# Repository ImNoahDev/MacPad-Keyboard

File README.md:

# The MacPad

The MacPad is a full sized keyboard designed for use with a Mac. The keyboard has 2 rotary encoders and a single fader for custom controls. The keyboard is designed to be used with QMK,

It can use any Alps or Cherry MX switches with optional through hole LEDs for backlighting.

## Assembly

The Plate must first be soldered underneath the switches (see plate.ai)

The PCB screws into the base with M3 screws and the top of the case screws ontop.

QMK firmware + configuration must be flashed using the macpad.hex file. The reset button can be pressed on the keyboard to put it into flashing mode and to flash the firmware. the F18 button can then be used as a reset button after the initial flash.

## BOM

| Item name         | Item price | Item use                                               | URL                                                                    |
| ----------------- | ---------- | ------------------------------------------------------ | ---------------------------------------------------------------------- |
| PCB               | $34        | PCB manufacture                                        | pcbway.com                                                             |
| PCB components    | $13        | Assemble controller on keyboard + rotary encoder/fader | pcbway.com                                                             |
| PCB Assembly      | $30        | Assemble PCB                                           | pcbway.com                                                             |
| Keyboard switches | $30        | Make the keyboard keyboard                             | [Keyswitches](https://www.keychron.uk/products/keychron-super-switch)  |
| Black fillament   | $24        | Print the case                                         | https://uk.store.bambulab.com/products/petg-hf?id=42010450329660       |
| Battery           | $10.78     | Battery power                                          | https://www.amazon.co.uk/EEMB-Battery-rechargeable-Connector-Certified |
| Total:            | $142.71    |                                                        |                                                                        |

## PCB component breakdown

| Designator                                                                                           | Quantity | Value                       | Footprint                               | Package | MPN                | DNP | Mount_Type | Description                                                                            | Price   | Total   | URL                                                                       |
| ---------------------------------------------------------------------------------------------------- | -------- | --------------------------- | --------------------------------------- | ------- | ------------------ | --- | ---------- | -------------------------------------------------------------------------------------- | ------- | ------- | ------------------------------------------------------------------------- |
| C1, C2                                                                                               | 2        | 22pF                        | C_0805_2012Metric                       |         |                    |     | smt        |                                                                                        | $0.0011 | $0.0022 | https://jlcpcb.com/partdetail/1907-0402CG220J500NT/C1555                  |
| C3                                                                                                   | 1        | 1uF                         | C_0805_2012Metric                       |         |                    |     | smt        |                                                                                        | $0.0032 | $0.0064 | https://jlcpcb.com/partdetail/1944-CL10A105KO8NNNC/C1592                  |
| C4, C5, C6                                                                                           | 3        | 0.1uF                       | C_0805_2012Metric                       |         |                    |     | smt        |                                                                                        | $0.0011 | $0.0033 | https://jlcpcb.com/partdetail/1877-CL05B104KO5NNNC/C1525                  |
| C7                                                                                                   | 1        | 10uF                        | C_0805_2012Metric                       |         |                    |     | smt        |                                                                                        | $0.0028 | $0.0028 | https://jlcpcb.com/partdetail/2043-CL10A106MQ8NNNC/C1691                  |
| D_0, D_1, D_10, D_100, D_101, D_102, D_103, D_104, D_105, D_106, D_107, D_108, D_11, D_12, D_13, D_14, D_15, D_16, D_17, D_18, D_19, D_2, D_20, D_21, D_22, D_23, D_24, D_25, D_26, D_27, D_28, D_29, D_3, D_30, D_31, D_32, D_33, D_34, D_35, D_36, D_37, D_38, D_39, D_4, D_40, D_41, D_42, D_43, D_44, D_45, D_46, D_47, D_48, D_49, D_5, D_50, D_51, D_52, D_53, D_54, D_55, D_56, D_57, D_58, D_59, D_6, D_60, D_61, D_62, D_63, D_64, D_65, D_66, D_67, D_68, D_69, D_7, D_70, D_71, D_72, D_73, D_74, D_75, D_76, D_77, D_78, D_79, D_8, D_80, D_81, D_82, D_83, D_84, D_85, D_86, D_87, D_88, D_89, D_9, D_90, D_91, D_92, D_93, D_94, D_95, D_96, D_97, D_98, D_99 | 109      | D                           | D_SOD-123                               |         |                    |     | smt        |                                                                                        | $0.0052 | $0.57   | https://jlcpcb.com/partdetail/Shunye-ES1D_SOD_123FL/C7370889              |
| F1                                                                                                   | 1        | 500mA                       | Fuse_1206_3216Metric                    |         |                    |     | smt        |                                                                                        | $0.0365 | $0.0365 | https://jlcpcb.com/partdetail/JlcpcbAssembly-FUSE/C9900021114             |
| J1                                                                                                   | 1        | USB_C_Receptacle_USB2.0_14P | USB_C_Receptacle_HCTL_HC-TYPE-C-16P-01A |         |                    |     | smt        | USB 2.0-only 14P Type-C Receptacle connector                                           | $0.0365 | $0.0365 | https://jlcpcb.com/partdetail/JlcpcbAssembly-14P/C9900117666              |
| Q1                                                                                                   | 1        | AO3400A                     | SOT-23                                  |         |                    |     | smt        | 30V Vds, 5.7A Id, N-Channel MOSFET, SOT-23                                             | $0.0428 | $0.0428 | https://jlcpcb.com/partdetail/Alpha_OmegaSemicon-AO3400A/C20917           |
| R1, R6, R7                                                                                           | 3        | 10k                         | R_0805_2012Metric                       |         |                    |     | smt        | Resistor                                                                               | $0.0013 | $0.0039 | https://jlcpcb.com/partdetail/1841-1206W4J0103T5E/C1489                   |
| R10, R100, R101, R102, R103, R104, R105, R106, R107, R108, R109, R11, R110, R111, R112, R113, R114, R115, R116, R117, R118, R12, R13, R14, R15, R16, R17, R18, R19, R20, R21, R22, R23, R24, R25, R26, R27, R28, R29, R30, R31, R32, R33, R34, R35, R36, R37, R38, R39, R40, R41, R42, R43, R44, R45, R46, R47, R48, R49, R50, R51, R52, R53, R54, R55, R56, R57, R58, R59, R60, R61, R62, R63, R64, R65, R66, R67, R68, R69, R70, R71, R72, R73, R74, R75, R76, R77, R78, R79, R80, R81, R82, R83, R84, R85, R86, R87, R88, R89, R90, R91, R92, R93, R94, R95, R96, R97, R98, R99 | 109      | 120                         | R_0805_2012Metric                       |         |                    |     | smt        | Resistor                                                                               | $0.0008 | $0.0872 | https://jlcpcb.com/partdetail/23514-0603WAF1200T5E/C22787                 |
| R2, R3                                                                                               | 2        | 5.1k                        | R_0805_2012Metric                       |         |                    |     | smt        |                                                                                        | $0.0007 | $0.0014 | https://jlcpcb.com/partdetail/Yageo-RC0603JR075K1L/C14677                 |
| R4, R5                                                                                               | 2        | 22                          | R_0805_2012Metric                       |         |                    |     | smt        |                                                                                        | $0.0005 | $0.001  | https://jlcpcb.com/partdetail/1555-0603WAJ0220T5E/C1203                   |
| R8                                                                                                   | 1        | 220                         | R_0805_2012Metric                       |         |                    |     | smt        | Resistor                                                                               | $0.0004 | $0.0004 | https://jlcpcb.com/partdetail/1463-RC02W221JT/C1111                       |
| SW1                                                                                                  | 1        | SW_Push                     | SKQG-1155865                            |         |                    |     | smt        |                                                                                        | $0.2385 | $0.2385 | https://jlcpcb.com/partdetail/Panasonic-EVQQ2B03W/C79178                  |
| U1                                                                                                   | 1        | RF-BM-ND06                  |                                         |         |                    |     | smt        |                                                                                        | $5      | $5      | https://jlcpcb.com/partdetail/rfstar-RF_BMND06/C5125838                   |
| U2, U3                                                                                               | 2        | EC11E18244A5                | EC11E18244A5_ALPS                       |         |                    |     | tht        |                                                                                        | $1.9785 | $3.96   | https://jlcpcb.com/partdetail/Alpsalpine-EC11E18244A5/C255515             |
| VR1                                                                                                  | 1        | PTB0143-2010BPB103          | PTB01432010BPB103                       |         | PTB0143-2010BPB103 |     | tht        | Bourns PTB0143-2010BPB103 1 Gang Slide Carbon Potentiometer, 10k, +/-20%, 0.5W, Linear | $5.5140 | $5.5140 | https://jlcpcb.com/partdetail/Bourns-PTB01432010BPB103/C17183742          |
| Y1                                                                                                   | 1        | 16MHz                       | Crystal_SMD_3225-4Pin_3.2x2.5mm         |         |                    |     | smt        |                                                                                        | $0.0356 | $0.0356 | https://jlcpcb.com/partdetail/Yxc_CrystalOscillators-X322516MOB4SI/C12668 |
|                                                                                                      |          |                             |                                         |         |                    |     |            |                                                                                        | Total:  | $23.93  |                                                                           |

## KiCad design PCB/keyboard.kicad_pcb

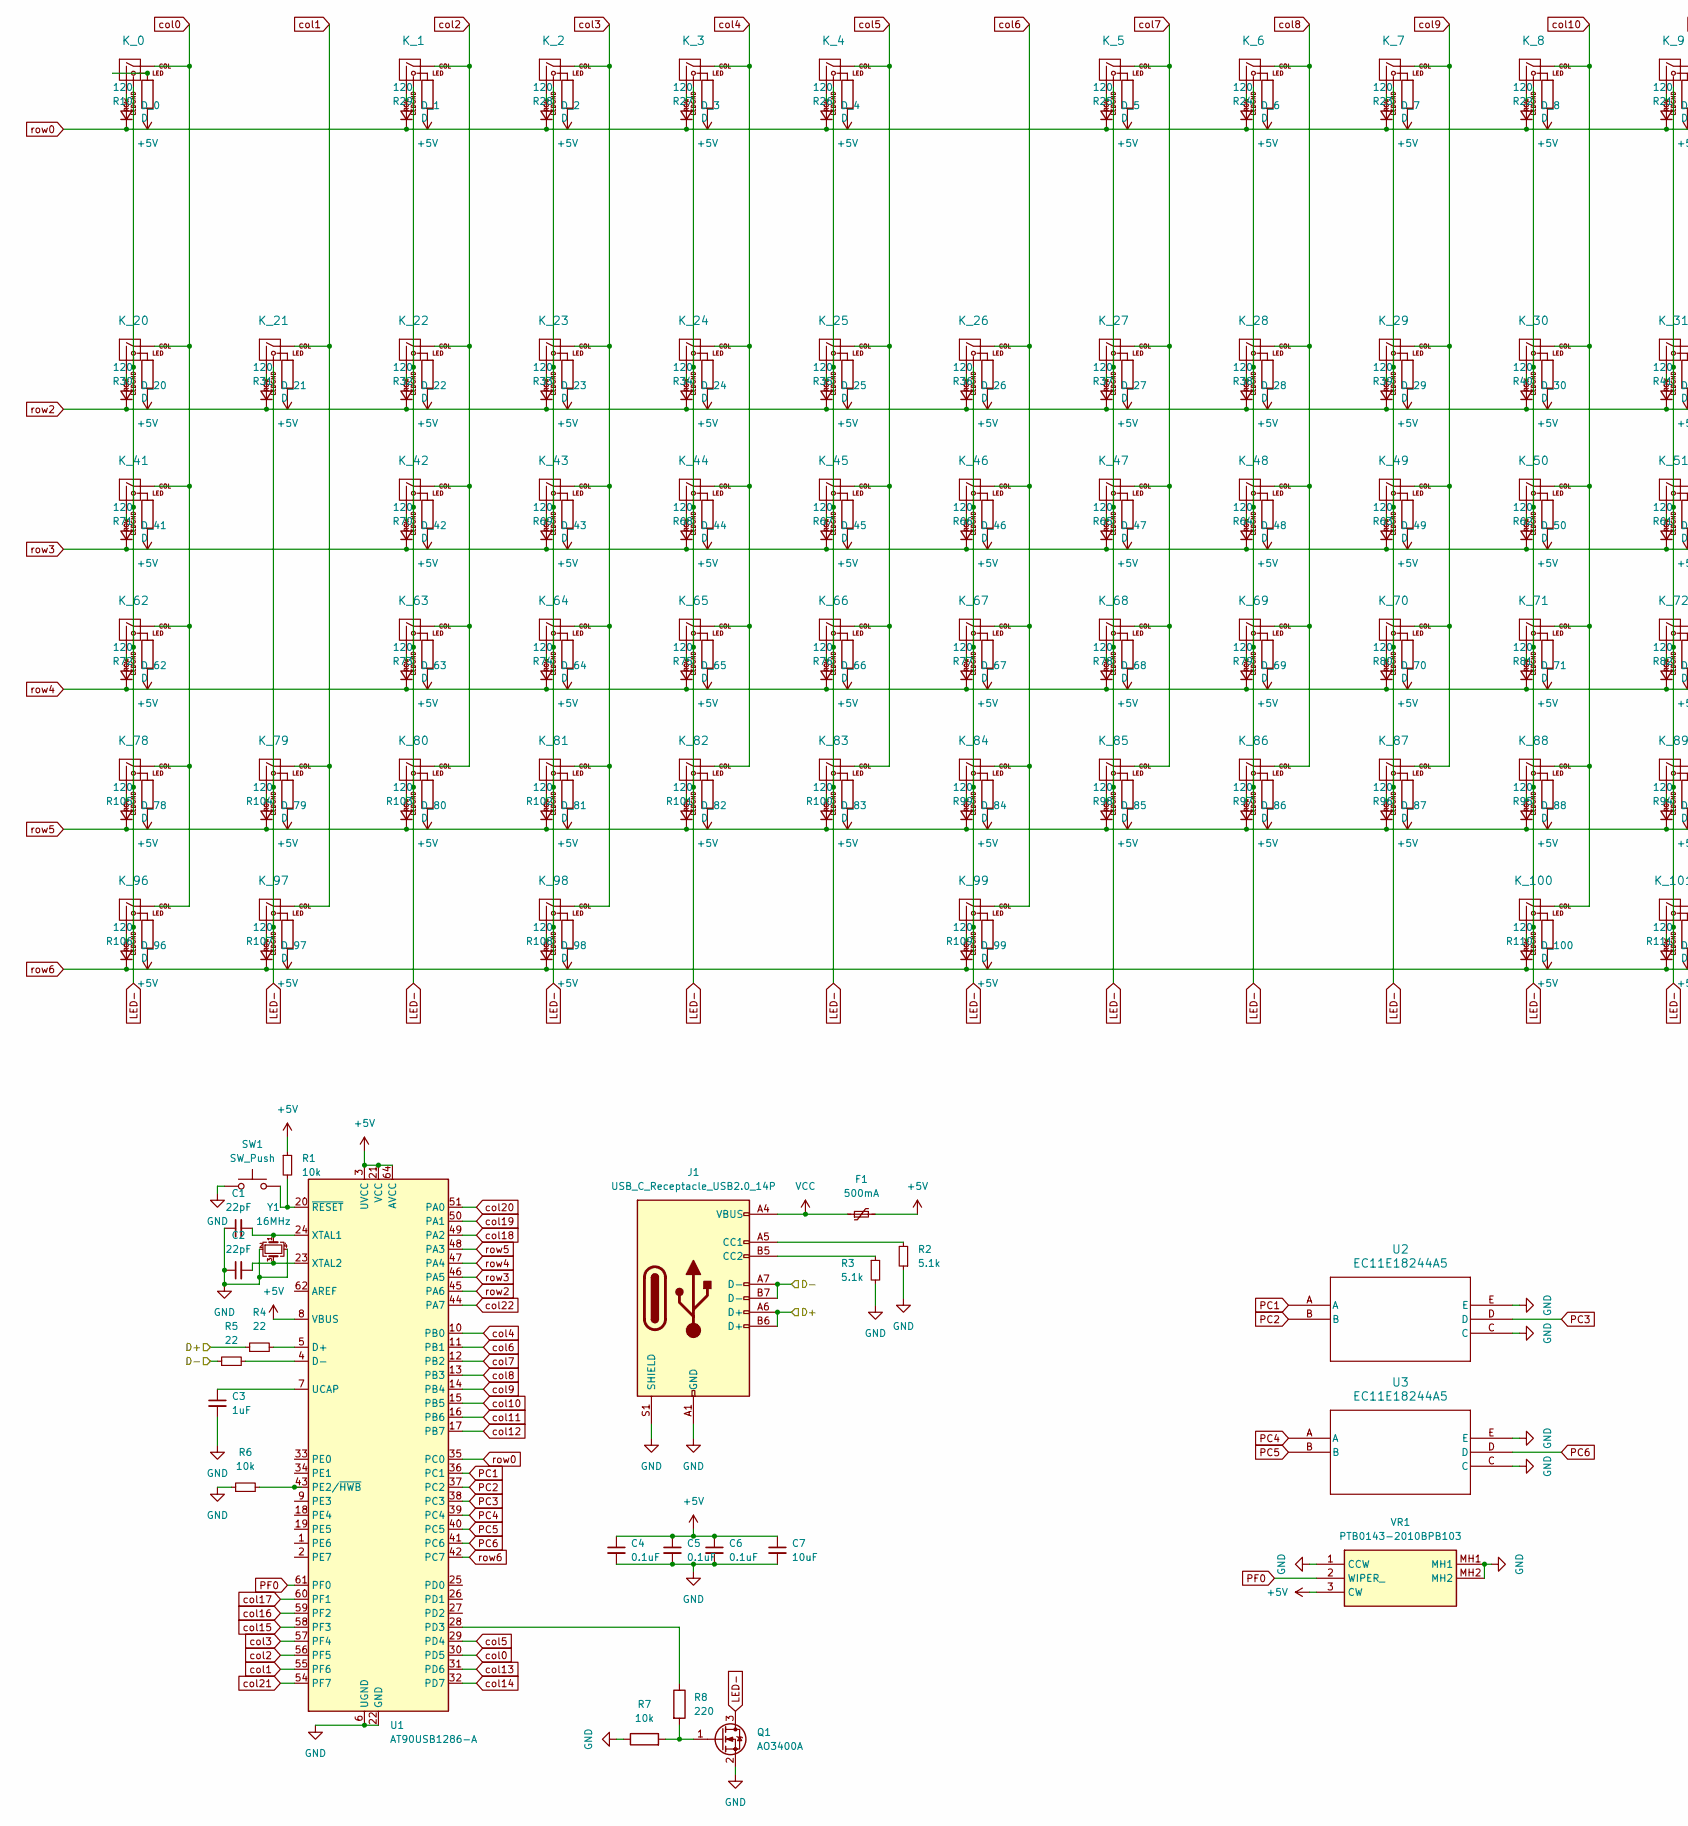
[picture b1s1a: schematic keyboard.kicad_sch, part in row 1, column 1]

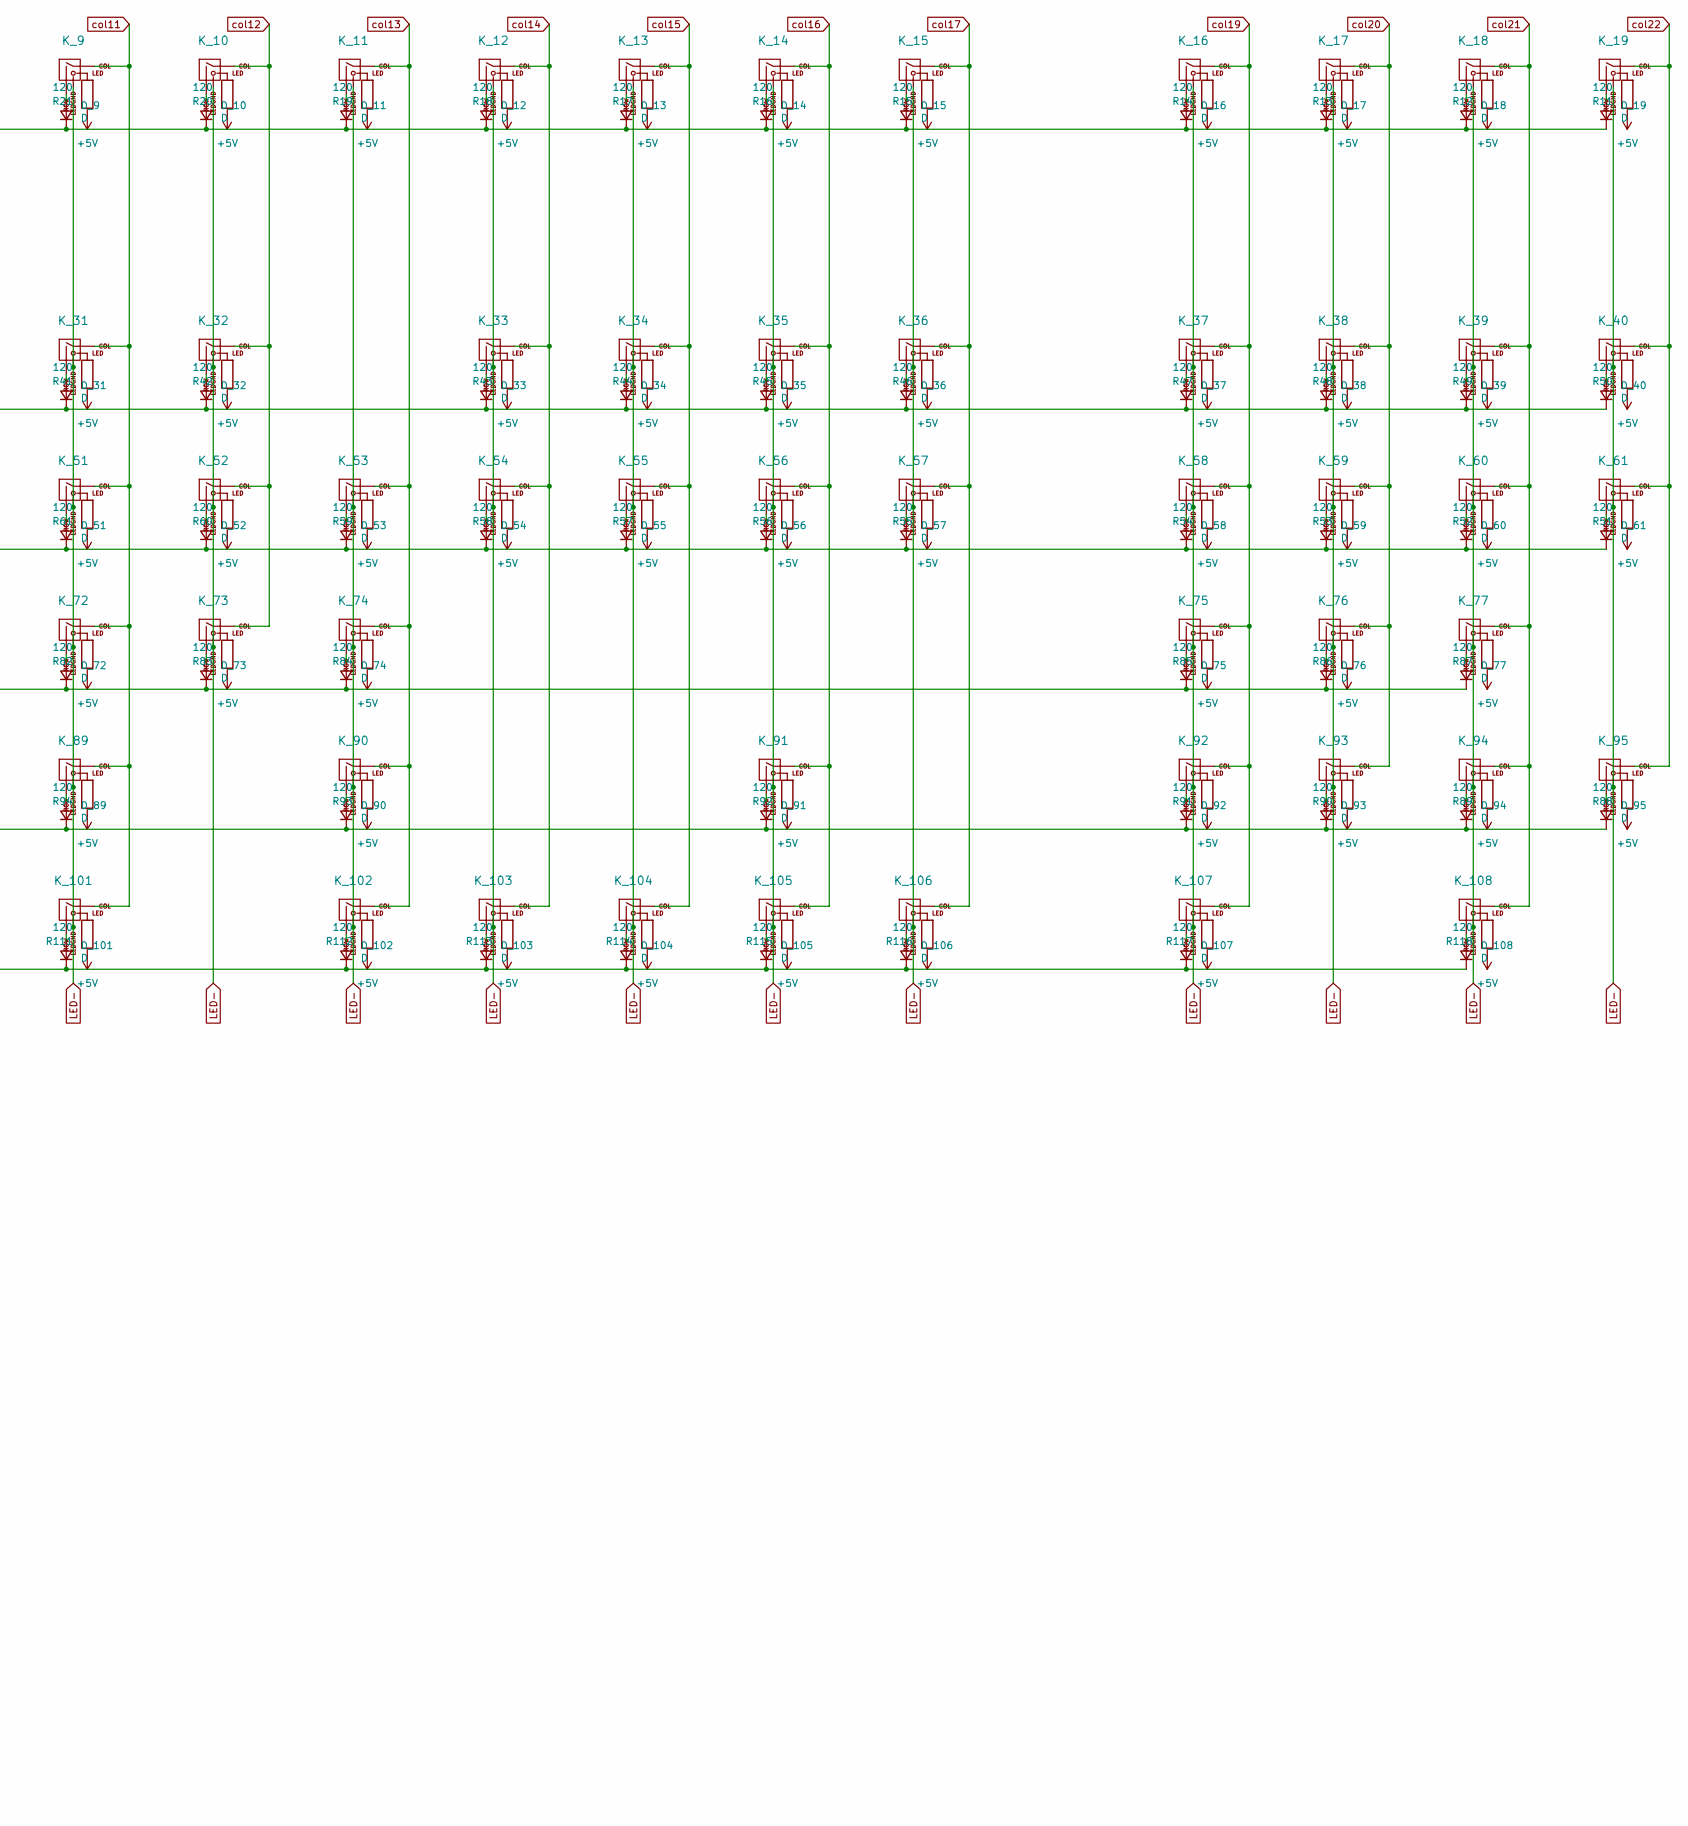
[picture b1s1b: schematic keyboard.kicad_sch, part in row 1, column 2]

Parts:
C1, C2: 22pF; C_0805_2012Metric
C3: 1uF; C_0805_2012Metric
C4, C5, C6: 0.1uF; C_0805_2012Metric
C7: 10uF; C_0805_2012Metric
D_0, D_1, D_2, D_3, D_4, D_5, D_6, D_7, D_8, D_9, D_10, D_11, D_12, D_13, D_14, D_15, D_16, D_17, D_18, D_19, D_20, D_21, D_22, D_23, D_24, D_25, D_26, D_27, D_28, D_29, D_30, D_31, D_32, D_33, D_34, D_35, D_36, D_37, D_38, D_39, D_40, D_41, D_42, D_43, D_44, D_45, D_46, D_47, D_48, D_49, D_50, D_51, D_52, D_53, D_54, D_55, D_56, D_57, D_58, D_59, D_60, D_61, D_62, D_63, D_64, D_65, D_66, D_67, D_68, D_69, D_70, D_71, D_72, D_73, D_74, D_75, D_76, D_77, D_78, D_79, D_80, D_81, D_82, D_83, D_84, D_85, D_86, D_87, D_88, D_89, D_90, D_91, D_92, D_93, D_94, D_95, D_96, D_97, D_98, D_99, D_100, D_101, D_102, D_103, D_104, D_105, D_106, D_107, D_108: D; D_SOD-123
F1: 500mA; Fuse_1206_3216Metric
J1: USB_C_Receptacle_USB2.0_14P; USB_C_Receptacle_HCTL_HC-TYPE-C-16P-01A
K_0, K_1, K_2, K_3, K_4, K_5, K_6, K_7, K_8, K_9, K_10, K_11, K_12, K_13, K_14, K_15, K_16, K_17, K_18, K_19, K_20, K_21, K_22, K_23, K_24, K_25, K_26, K_27, K_28, K_29, K_30, K_31, K_32, K_34, K_35, K_36, K_37, K_38, K_39, K_40, K_42, K_43, K_44, K_45, K_46, K_47, K_48, K_49, K_50, K_51, K_52, K_53, K_55, K_56, K_57, K_58, K_59, K_60, K_63, K_64, K_65, K_66, K_67, K_68, K_69, K_70, K_71, K_72, K_73, K_74, K_75, K_76, K_77, K_79, K_80, K_81, K_82, K_83, K_84, K_85, K_86, K_87, K_88, K_89, K_91, K_92, K_93, K_94, K_104, K_105, K_106, K_108: KEYSW; MX-1U
K_33, K_107: KEYSW; MX-2U
K_41: KEYSW; MX-1.5U
K_54: KEYSW; MX-ISO
K_61, K_95: KEYSW; MXOnly-2U
K_62: KEYSW; MX-1.75U
K_78, K_96, K_97, K_98, K_100, K_101, K_102, K_103: KEYSW; MX-1.25U
K_90: KEYSW; MX-2.75U
K_99: KEYSW; MX-6.25U
Q1: AO3400A; SOT-23
R1, R6, R7: 10k; R_0805_2012Metric
R2, R3: 5.1k; R_0805_2012Metric
R4, R5: 22; R_0805_2012Metric
R8: 220; R_0805_2012Metric
R10, R11, R12, R13, R14, R15, R16, R17, R18, R19, R20, R21, R22, R23, R24, R25, R26, R27, R28, R29, R30, R31, R32, R33, R34, R35, R36, R37, R38, R39, R40, R41, R42, R43, R44, R45, R46, R47, R48, R49, R50, R51, R52, R53, R54, R55, R56, R57, R58, R59, R60, R61, R62, R63, R64, R65, R66, R67, R68, R69, R70, R71, R72, R73, R74, R75, R76, R77, R78, R79, R80, R81, R82, R83, R84, R85, R86, R87, R88, R89, R90, R91, R92, R93, R94, R95, R96, R97, R98, R99, R100, R101, R102, R103, R104, R105, R106, R107, R108, R109, R110, R111, R112, R113, R114, R115, R116, R117, R118: 120; R_0805_2012Metric
SW1: SW_Push; SKQG-1155865
U1: AT90USB1286-A; TQFP-64_14x14mm_P0.8mm
U2, U3: EC11E18244A5; EC11E18244A5_ALPS
VR1: PTB0143-2010BPB103; PTB01432010BPB103; Mouser Part Number 652-PTB1432010BPB103
Y1: 16MHz; Crystal_SMD_3225-4Pin_3.2x2.5mm

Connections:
+5V: C4.1, C5.1, C6.1, C7.1, F1.2, R1.1, R10.1, R11.1, R12.1, R13.1, R14.1, R15.1, R16.1, R17.1, R18.1, R19.1, R20.1, R21.1, R22.1, R23.1, R24.1, R25.1, R26.1, R27.1, R28.1, R29.1, R30.1, R31.1, R32.1, R33.1, R34.1, R35.1, R36.1, R37.1, R38.1, R39.1, R40.1, R41.1, R42.1, R43.1, R44.1, R45.1, R46.1, R47.1, R48.1, R49.1, R50.1, R51.1, R52.1, R53.1, R54.1, R55.1, R56.1, R57.1, R58.1, R59.1, R60.1, R61.1, R62.1, R63.1, R64.1, R65.1, R66.1, R67.1, R68.1, R69.1, R70.1, R71.1, R72.1, R73.1, R74.1, R75.1, R76.1, R77.1, R78.1, R79.1, R80.1, R81.1, R82.1, R83.1, R84.1, R85.1, R86.1, R87.1, R88.1, R89.1, R90.1, R91.1, R92.1, R93.1, R94.1, R95.1, R96.1, R97.1, R98.1, R99.1, R100.1, R101.1, R102.1, R103.1, R104.1, R105.1, R106.1, R107.1, R108.1, R109.1, R110.1, R111.1, R112.1, R113.1, R114.1, R115.1, R116.1, R117.1, R118.1, U1.3 (UVCC), U1.8 (VBUS), U1.21 (VCC), U1.52 (VCC), U1.64 (AVCC), VR1.3 (CW)
/D+: J1.A6 (D+), J1.B6 (D+), R4.1
/D-: J1.A7 (D-), J1.B7 (D-), R5.1
GND: C1.1, C2.1, C3.2, C4.2, C5.2, C6.2, C7.2, J1.A1 (GND), J1.A12 (GND), J1.B1 (GND), J1.B12 (GND), J1.S1 (SHIELD), Q1.2 (S), R2.1, R3.2, R6.1, R7.1, SW1.1, U1.6 (UGND), U1.22 (GND), U1.53 (GND), U1.63 (GND), U2.C, U2.E, U3.C, U3.E, VR1.1 (CCW), VR1.MH1, VR1.MH2, Y1.2, Y1.4
LED-: K_0.4 (LEDGND), K_1.4 (LEDGND), K_2.4 (LEDGND), K_3.4 (LEDGND), K_4.4 (LEDGND), K_5.4 (LEDGND), K_6.4 (LEDGND), K_7.4 (LEDGND), K_8.4 (LEDGND), K_9.4 (LEDGND), K_10.4 (LEDGND), K_11.4 (LEDGND), K_12.4 (LEDGND), K_13.4 (LEDGND), K_14.4 (LEDGND), K_15.4 (LEDGND), K_16.4 (LEDGND), K_17.4 (LEDGND), K_18.4 (LEDGND), K_19.4 (LEDGND), K_20.4 (LEDGND), K_21.4 (LEDGND), K_22.4 (LEDGND), K_23.4 (LEDGND), K_24.4 (LEDGND), K_25.4 (LEDGND), K_26.4 (LEDGND), K_27.4 (LEDGND), K_28.4 (LEDGND), K_29.4 (LEDGND), K_30.4 (LEDGND), K_31.4 (LEDGND), K_32.4 (LEDGND), K_33.4 (LEDGND), K_34.4 (LEDGND), K_35.4 (LEDGND), K_36.4 (LEDGND), K_37.4 (LEDGND), K_38.4 (LEDGND), K_39.4 (LEDGND), K_40.4 (LEDGND), K_41.4 (LEDGND), K_42.4 (LEDGND), K_43.4 (LEDGND), K_44.4 (LEDGND), K_45.4 (LEDGND), K_46.4 (LEDGND), K_47.4 (LEDGND), K_48.4 (LEDGND), K_49.4 (LEDGND), K_50.4 (LEDGND), K_51.4 (LEDGND), K_52.4 (LEDGND), K_53.4 (LEDGND), K_54.4 (LEDGND), K_55.4 (LEDGND), K_56.4 (LEDGND), K_57.4 (LEDGND), K_58.4 (LEDGND), K_59.4 (LEDGND), K_60.4 (LEDGND), K_61.4 (LEDGND), K_62.4 (LEDGND), K_63.4 (LEDGND), K_64.4 (LEDGND), K_65.4 (LEDGND), K_66.4 (LEDGND), K_67.4 (LEDGND), K_68.4 (LEDGND), K_69.4 (LEDGND), K_70.4 (LEDGND), K_71.4 (LEDGND), K_72.4 (LEDGND), K_73.4 (LEDGND), K_74.4 (LEDGND), K_75.4 (LEDGND), K_76.4 (LEDGND), K_77.4 (LEDGND), K_78.4 (LEDGND), K_79.4 (LEDGND), K_80.4 (LEDGND), K_81.4 (LEDGND), K_82.4 (LEDGND), K_83.4 (LEDGND), K_84.4 (LEDGND), K_85.4 (LEDGND), K_86.4 (LEDGND), K_87.4 (LEDGND), K_88.4 (LEDGND), K_89.4 (LEDGND), K_90.4 (LEDGND), K_91.4 (LEDGND), K_92.4 (LEDGND), K_93.4 (LEDGND), K_94.4 (LEDGND), K_95.4 (LEDGND), K_96.4 (LEDGND), K_97.4 (LEDGND), K_98.4 (LEDGND), K_99.4 (LEDGND), K_100.4 (LEDGND), K_101.4 (LEDGND), K_102.4 (LEDGND), K_103.4 (LEDGND), K_104.4 (LEDGND), K_105.4 (LEDGND), K_106.4 (LEDGND), K_107.4 (LEDGND), K_108.4 (LEDGND), Q1.3 (D)
unnamed: D_0.2 (A), K_0.2 (ROW)
unnamed: D_1.2 (A), K_1.2 (ROW)
unnamed: D_2.2 (A), K_2.2 (ROW)
unnamed: D_3.2 (A), K_3.2 (ROW)
unnamed: D_4.2 (A), K_4.2 (ROW)
unnamed: D_5.2 (A), K_5.2 (ROW)
unnamed: D_6.2 (A), K_6.2 (ROW)
unnamed: D_7.2 (A), K_7.2 (ROW)
unnamed: D_8.2 (A), K_8.2 (ROW)
unnamed: D_9.2 (A), K_9.2 (ROW)
unnamed: D_10.2 (A), K_10.2 (ROW)
unnamed: D_11.2 (A), K_11.2 (ROW)
unnamed: D_12.2 (A), K_12.2 (ROW)
unnamed: D_13.2 (A), K_13.2 (ROW)
unnamed: D_14.2 (A), K_14.2 (ROW)
unnamed: D_15.2 (A), K_15.2 (ROW)
unnamed: D_16.2 (A), K_16.2 (ROW)
unnamed: D_17.2 (A), K_17.2 (ROW)
unnamed: D_18.2 (A), K_18.2 (ROW)
unnamed: D_19.2 (A), K_19.2 (ROW)
unnamed: D_20.2 (A), K_20.2 (ROW)
unnamed: D_21.2 (A), K_21.2 (ROW)
unnamed: D_22.2 (A), K_22.2 (ROW)
unnamed: D_23.2 (A), K_23.2 (ROW)
unnamed: D_24.2 (A), K_24.2 (ROW)
unnamed: D_25.2 (A), K_25.2 (ROW)
unnamed: D_26.2 (A), K_26.2 (ROW)
unnamed: D_27.2 (A), K_27.2 (ROW)
unnamed: D_28.2 (A), K_28.2 (ROW)
unnamed: D_29.2 (A), K_29.2 (ROW)
unnamed: D_30.2 (A), K_30.2 (ROW)
unnamed: D_31.2 (A), K_31.2 (ROW)
unnamed: D_32.2 (A), K_32.2 (ROW)
unnamed: D_33.2 (A), K_33.2 (ROW)
unnamed: D_34.2 (A), K_34.2 (ROW)
unnamed: D_35.2 (A), K_35.2 (ROW)
unnamed: D_36.2 (A), K_36.2 (ROW)
unnamed: D_37.2 (A), K_37.2 (ROW)
unnamed: D_38.2 (A), K_38.2 (ROW)
unnamed: D_39.2 (A), K_39.2 (ROW)
unnamed: D_40.2 (A), K_40.2 (ROW)
unnamed: D_41.2 (A), K_41.2 (ROW)
unnamed: D_42.2 (A), K_42.2 (ROW)
unnamed: D_43.2 (A), K_43.2 (ROW)
unnamed: D_44.2 (A), K_44.2 (ROW)
unnamed: D_45.2 (A), K_45.2 (ROW)
unnamed: D_46.2 (A), K_46.2 (ROW)
unnamed: D_47.2 (A), K_47.2 (ROW)
unnamed: D_48.2 (A), K_48.2 (ROW)
unnamed: D_49.2 (A), K_49.2 (ROW)
unnamed: D_50.2 (A), K_50.2 (ROW)
unnamed: D_51.2 (A), K_51.2 (ROW)
unnamed: D_52.2 (A), K_52.2 (ROW)
unnamed: D_53.2 (A), K_53.2 (ROW)
unnamed: D_54.2 (A), K_54.2 (ROW)
unnamed: D_55.2 (A), K_55.2 (ROW)
unnamed: D_56.2 (A), K_56.2 (ROW)
unnamed: D_57.2 (A), K_57.2 (ROW)
unnamed: D_58.2 (A), K_58.2 (ROW)
unnamed: D_59.2 (A), K_59.2 (ROW)
unnamed: D_60.2 (A), K_60.2 (ROW)
unnamed: D_61.2 (A), K_61.2 (ROW)
unnamed: D_62.2 (A), K_62.2 (ROW)
unnamed: D_63.2 (A), K_63.2 (ROW)
unnamed: D_64.2 (A), K_64.2 (ROW)
unnamed: D_65.2 (A), K_65.2 (ROW)
unnamed: D_66.2 (A), K_66.2 (ROW)
unnamed: D_67.2 (A), K_67.2 (ROW)
unnamed: D_68.2 (A), K_68.2 (ROW)
unnamed: D_69.2 (A), K_69.2 (ROW)
unnamed: D_70.2 (A), K_70.2 (ROW)
unnamed: D_71.2 (A), K_71.2 (ROW)
unnamed: D_72.2 (A), K_72.2 (ROW)
unnamed: D_73.2 (A), K_73.2 (ROW)
unnamed: D_74.2 (A), K_74.2 (ROW)
unnamed: D_75.2 (A), K_75.2 (ROW)
unnamed: D_76.2 (A), K_76.2 (ROW)
unnamed: D_77.2 (A), K_77.2 (ROW)
unnamed: D_78.2 (A), K_78.2 (ROW)
unnamed: D_79.2 (A), K_79.2 (ROW)
unnamed: D_80.2 (A), K_80.2 (ROW)
unnamed: D_81.2 (A), K_81.2 (ROW)
unnamed: D_82.2 (A), K_82.2 (ROW)
unnamed: D_83.2 (A), K_83.2 (ROW)
unnamed: D_84.2 (A), K_84.2 (ROW)
unnamed: D_85.2 (A), K_85.2 (ROW)
unnamed: D_86.2 (A), K_86.2 (ROW)
unnamed: D_87.2 (A), K_87.2 (ROW)
unnamed: D_88.2 (A), K_88.2 (ROW)
unnamed: D_89.2 (A), K_89.2 (ROW)
unnamed: D_90.2 (A), K_90.2 (ROW)
unnamed: D_91.2 (A), K_91.2 (ROW)
unnamed: D_92.2 (A), K_92.2 (ROW)
unnamed: D_93.2 (A), K_93.2 (ROW)
unnamed: D_94.2 (A), K_94.2 (ROW)
unnamed: D_95.2 (A), K_95.2 (ROW)
unnamed: D_96.2 (A), K_96.2 (ROW)
unnamed: D_97.2 (A), K_97.2 (ROW)
unnamed: D_98.2 (A), K_98.2 (ROW)
unnamed: D_99.2 (A), K_99.2 (ROW)
unnamed: D_100.2 (A), K_100.2 (ROW)
unnamed: D_101.2 (A), K_101.2 (ROW)
unnamed: D_102.2 (A), K_102.2 (ROW)
unnamed: D_103.2 (A), K_103.2 (ROW)
unnamed: D_104.2 (A), K_104.2 (ROW)
unnamed: D_105.2 (A), K_105.2 (ROW)
unnamed: D_106.2 (A), K_106.2 (ROW)
unnamed: D_107.2 (A), K_107.2 (ROW)
unnamed: D_108.2 (A), K_108.2 (ROW)
unnamed: J1.A5 (CC1), R2.2
unnamed: J1.B5 (CC2), R3.1
unnamed: K_0.3 (LED), R10.2
unnamed: K_1.3 (LED), R29.2
unnamed: K_2.3 (LED), R28.2
unnamed: K_3.3 (LED), R27.2
unnamed: K_4.3 (LED), R26.2
unnamed: K_5.3 (LED), R25.2
unnamed: K_6.3 (LED), R24.2
unnamed: K_7.3 (LED), R23.2
unnamed: K_8.3 (LED), R22.2
unnamed: K_9.3 (LED), R21.2
unnamed: K_10.3 (LED), R20.2
unnamed: K_11.3 (LED), R19.2
unnamed: K_12.3 (LED), R18.2
unnamed: K_13.3 (LED), R17.2
unnamed: K_14.3 (LED), R16.2
unnamed: K_15.3 (LED), R15.2
unnamed: K_16.3 (LED), R14.2
unnamed: K_17.3 (LED), R13.2
unnamed: K_18.3 (LED), R12.2
unnamed: K_19.3 (LED), R11.2
unnamed: K_20.3 (LED), R30.2
unnamed: K_21.3 (LED), R31.2
unnamed: K_22.3 (LED), R32.2
unnamed: K_23.3 (LED), R33.2
unnamed: K_24.3 (LED), R34.2
unnamed: K_25.3 (LED), R35.2
unnamed: K_26.3 (LED), R36.2
unnamed: K_27.3 (LED), R37.2
unnamed: K_28.3 (LED), R38.2
unnamed: K_29.3 (LED), R39.2
unnamed: K_30.3 (LED), R40.2
unnamed: K_31.3 (LED), R41.2
unnamed: K_32.3 (LED), R42.2
unnamed: K_33.3 (LED), R43.2
unnamed: K_34.3 (LED), R44.2
unnamed: K_35.3 (LED), R45.2
unnamed: K_36.3 (LED), R46.2
unnamed: K_37.3 (LED), R47.2
unnamed: K_38.3 (LED), R48.2
unnamed: K_39.3 (LED), R49.2
unnamed: K_40.3 (LED), R50.2
unnamed: K_41.3 (LED), R71.2
unnamed: K_42.3 (LED), R70.2
unnamed: K_43.3 (LED), R69.2
unnamed: K_44.3 (LED), R68.2
unnamed: K_45.3 (LED), R67.2
unnamed: K_46.3 (LED), R66.2
unnamed: K_47.3 (LED), R65.2
unnamed: K_48.3 (LED), R64.2
unnamed: K_49.3 (LED), R63.2
unnamed: K_50.3 (LED), R62.2
unnamed: K_51.3 (LED), R61.2
unnamed: K_52.3 (LED), R60.2
unnamed: K_53.3 (LED), R59.2
unnamed: K_54.3 (LED), R58.2
unnamed: K_55.3 (LED), R57.2
unnamed: K_56.3 (LED), R56.2
unnamed: K_57.3 (LED), R55.2
unnamed: K_58.3 (LED), R54.2
unnamed: K_59.3 (LED), R53.2
unnamed: K_60.3 (LED), R52.2
unnamed: K_61.3 (LED), R51.2
unnamed: K_62.3 (LED), R72.2
unnamed: K_63.3 (LED), R73.2
unnamed: K_64.3 (LED), R74.2
unnamed: K_65.3 (LED), R75.2
unnamed: K_66.3 (LED), R76.2
unnamed: K_67.3 (LED), R77.2
unnamed: K_68.3 (LED), R78.2
unnamed: K_69.3 (LED), R79.2
unnamed: K_70.3 (LED), R80.2
unnamed: K_71.3 (LED), R81.2
unnamed: K_72.3 (LED), R82.2
unnamed: K_73.3 (LED), R83.2
unnamed: K_74.3 (LED), R84.2
unnamed: K_75.3 (LED), R85.2
unnamed: K_76.3 (LED), R86.2
unnamed: K_77.3 (LED), R87.2
unnamed: K_78.3 (LED), R105.2
unnamed: K_79.3 (LED), R104.2
unnamed: K_80.3 (LED), R103.2
unnamed: K_81.3 (LED), R102.2
unnamed: K_82.3 (LED), R101.2
unnamed: K_83.3 (LED), R100.2
unnamed: K_84.3 (LED), R99.2
unnamed: K_85.3 (LED), R98.2
unnamed: K_86.3 (LED), R97.2
unnamed: K_87.3 (LED), R96.2
unnamed: K_88.3 (LED), R95.2
unnamed: K_89.3 (LED), R94.2
unnamed: K_90.3 (LED), R93.2
unnamed: K_91.3 (LED), R92.2
unnamed: K_92.3 (LED), R91.2
unnamed: K_93.3 (LED), R90.2
unnamed: K_94.3 (LED), R89.2
unnamed: K_95.3 (LED), R88.2
unnamed: K_96.3 (LED), R106.2
unnamed: K_97.3 (LED), R107.2
unnamed: K_98.3 (LED), R108.2
unnamed: K_99.3 (LED), R109.2
unnamed: K_100.3 (LED), R110.2
unnamed: K_101.3 (LED), R111.2
unnamed: K_102.3 (LED), R112.2
unnamed: K_103.3 (LED), R113.2
unnamed: K_104.3 (LED), R114.2
unnamed: K_105.3 (LED), R115.2
unnamed: K_106.3 (LED), R116.2
unnamed: K_107.3 (LED), R117.2
unnamed: K_108.3 (LED), R118.2
unnamed: Q1.1 (G), R7.2, R8.2
unnamed: R4.2, U1.5 (D+)
unnamed: R5.2, U1.4 (D-)
unnamed: R8.1, U1.28 (PD3)
unnamed: R6.2, U1.43 (PE2/~HWB)
unnamed: C3.1, U1.7 (UCAP)
unnamed: C1.2, U1.24 (XTAL1), Y1.1
unnamed: C2.2, U1.23 (XTAL2), Y1.3
unnamed: R1.2, SW1.2, U1.20 (~RESET)
PC1: U1.36 (PC1), U2.A
PC2: U1.37 (PC2), U2.B
PC3: U1.38 (PC3), U2.D
PC4: U1.39 (PC4), U3.A
PC5: U1.40 (PC5), U3.B
PC6: U1.41 (PC6), U3.D
PF0: U1.61 (PF0), VR1.2 (WIPER_)
VCC: F1.1, J1.A4 (VBUS), J1.A9 (VBUS), J1.B4 (VBUS), J1.B9 (VBUS)
col0: K_0.1 (COL), K_20.1 (COL), K_41.1 (COL), K_62.1 (COL), K_78.1 (COL), K_96.1 (COL), U1.30 (PD5)
col1: K_21.1 (COL), K_79.1 (COL), K_97.1 (COL), U1.55 (PF6)
col2: K_1.1 (COL), K_22.1 (COL), K_42.1 (COL), K_63.1 (COL), K_80.1 (COL), U1.56 (PF5)
col3: K_2.1 (COL), K_23.1 (COL), K_43.1 (COL), K_64.1 (COL), K_81.1 (COL), K_98.1 (COL), U1.57 (PF4)
col4: K_3.1 (COL), K_24.1 (COL), K_44.1 (COL), K_65.1 (COL), K_82.1 (COL), U1.10 (PB0)
col5: K_4.1 (COL), K_25.1 (COL), K_45.1 (COL), K_66.1 (COL), K_83.1 (COL), U1.29 (PD4)
col6: K_26.1 (COL), K_46.1 (COL), K_67.1 (COL), K_84.1 (COL), K_99.1 (COL), U1.11 (PB1)
col7: K_5.1 (COL), K_27.1 (COL), K_47.1 (COL), K_68.1 (COL), K_85.1 (COL), U1.12 (PB2)
col8: K_6.1 (COL), K_28.1 (COL), K_48.1 (COL), K_69.1 (COL), K_86.1 (COL), U1.13 (PB3)
col9: K_7.1 (COL), K_29.1 (COL), K_49.1 (COL), K_70.1 (COL), K_87.1 (COL), U1.14 (PB4)
col10: K_8.1 (COL), K_30.1 (COL), K_50.1 (COL), K_71.1 (COL), K_88.1 (COL), K_100.1 (COL), U1.15 (PB5)
col11: K_9.1 (COL), K_31.1 (COL), K_51.1 (COL), K_72.1 (COL), K_89.1 (COL), K_101.1 (COL), U1.16 (PB6)
col12: K_10.1 (COL), K_32.1 (COL), K_52.1 (COL), K_73.1 (COL), U1.17 (PB7)
col13: K_11.1 (COL), K_53.1 (COL), K_74.1 (COL), K_90.1 (COL), K_102.1 (COL), U1.31 (PD6)
col14: K_12.1 (COL), K_33.1 (COL), K_54.1 (COL), K_103.1 (COL), U1.32 (PD7)
col15: K_13.1 (COL), K_34.1 (COL), K_55.1 (COL), K_104.1 (COL), U1.58 (PF3)
col16: K_14.1 (COL), K_35.1 (COL), K_56.1 (COL), K_91.1 (COL), K_105.1 (COL), U1.59 (PF2)
col17: K_15.1 (COL), K_36.1 (COL), K_57.1 (COL), K_106.1 (COL), U1.60 (PF1)
col18: U1.49 (PA2)
col19: K_16.1 (COL), K_37.1 (COL), K_58.1 (COL), K_75.1 (COL), K_92.1 (COL), K_107.1 (COL), U1.50 (PA1)
col20: K_17.1 (COL), K_38.1 (COL), K_59.1 (COL), K_76.1 (COL), K_93.1 (COL), U1.51 (PA0)
col21: K_18.1 (COL), K_39.1 (COL), K_60.1 (COL), K_77.1 (COL), K_94.1 (COL), K_108.1 (COL), U1.54 (PF7)
col22: K_19.1 (COL), K_40.1 (COL), K_61.1 (COL), K_95.1 (COL), U1.44 (PA7)
row0: D_0.1 (K), D_1.1 (K), D_2.1 (K), D_3.1 (K), D_4.1 (K), D_5.1 (K), D_6.1 (K), D_7.1 (K), D_8.1 (K), D_9.1 (K), D_10.1 (K), D_11.1 (K), D_12.1 (K), D_13.1 (K), D_14.1 (K), D_15.1 (K), D_16.1 (K), D_17.1 (K), D_18.1 (K), D_19.1 (K), U1.35 (PC0)
row2: D_20.1 (K), D_21.1 (K), D_22.1 (K), D_23.1 (K), D_24.1 (K), D_25.1 (K), D_26.1 (K), D_27.1 (K), D_28.1 (K), D_29.1 (K), D_30.1 (K), D_31.1 (K), D_32.1 (K), D_33.1 (K), D_34.1 (K), D_35.1 (K), D_36.1 (K), D_37.1 (K), D_38.1 (K), D_39.1 (K), D_40.1 (K), U1.45 (PA6)
row3: D_41.1 (K), D_42.1 (K), D_43.1 (K), D_44.1 (K), D_45.1 (K), D_46.1 (K), D_47.1 (K), D_48.1 (K), D_49.1 (K), D_50.1 (K), D_51.1 (K), D_52.1 (K), D_53.1 (K), D_54.1 (K), D_55.1 (K), D_56.1 (K), D_57.1 (K), D_58.1 (K), D_59.1 (K), D_60.1 (K), D_61.1 (K), U1.46 (PA5)
row4: D_62.1 (K), D_63.1 (K), D_64.1 (K), D_65.1 (K), D_66.1 (K), D_67.1 (K), D_68.1 (K), D_69.1 (K), D_70.1 (K), D_71.1 (K), D_72.1 (K), D_73.1 (K), D_74.1 (K), D_75.1 (K), D_76.1 (K), D_77.1 (K), U1.47 (PA4)
row5: D_78.1 (K), D_79.1 (K), D_80.1 (K), D_81.1 (K), D_82.1 (K), D_83.1 (K), D_84.1 (K), D_85.1 (K), D_86.1 (K), D_87.1 (K), D_88.1 (K), D_89.1 (K), D_90.1 (K), D_91.1 (K), D_92.1 (K), D_93.1 (K), D_94.1 (K), D_95.1 (K), U1.48 (PA3)
row6: D_96.1 (K), D_97.1 (K), D_98.1 (K), D_99.1 (K), D_100.1 (K), D_101.1 (K), D_102.1 (K), D_103.1 (K), D_104.1 (K), D_105.1 (K), D_106.1 (K), D_107.1 (K), D_108.1 (K), U1.42 (PC7)
